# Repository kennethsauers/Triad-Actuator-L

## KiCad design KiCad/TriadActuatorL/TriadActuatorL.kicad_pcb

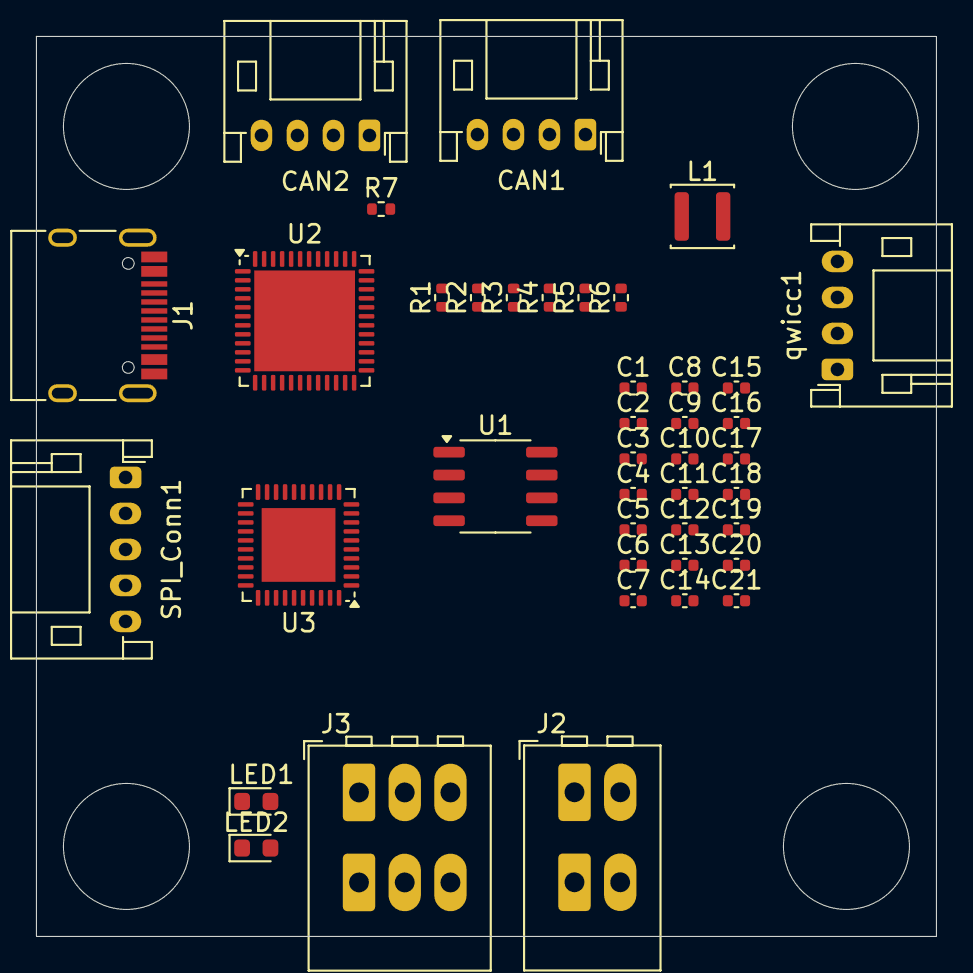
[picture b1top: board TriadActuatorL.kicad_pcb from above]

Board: 2 copper layers, 50.0 x 50.0 mm, 41 parts (0 on the bottom side), 35 nets, no tracks yet.

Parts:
C1, C3, C5, C19, C20: 1uF; C_0402_1005Metric
C2, C4, C6, C7, C21: 100nF; C_0402_1005Metric
C8, C9, C10, C11, C12, C13: 10uF; C_0402_1005Metric
C14, C15, C16: 30pF; C_0402_1005Metric
C17: 22uF; C_0402_1005Metric
C18: 47nF; C_0402_1005Metric
CAN1, CAN2: Conn_01x04_Pin; JST_PH_S4B-PH-K_1x04_P2.00mm_Horizontal
J1: USB_C_Receptacle_USB2.0_16P; USB_C_Receptacle_HRO_TYPE-C-31-M-12
J2: Motor Terminal; TerminalBlock_WAGO_233-502_2x02_P2.54mm
J3: PWR Terminal; TerminalBlock_WAGO_233-503_2x03_P2.54mm
L1: 47uH; L_APV_ANR3015
LED1: red; LED_0603_1608Metric
LED2: blue; LED_0603_1608Metric
R1, R2, R3: 5.1k; R_0402_1005Metric
R4: 330; R_0402_1005Metric
R5, R6, R7: 1000; R_0402_1005Metric
SPI_Conn1: Conn_01x05_Pin; JST_PH_S5B-PH-K_1x05_P2.00mm_Horizontal
U1: MT6701CT; SO-8_3.9x4.9mm_P1.27mm
U2: STM32G431C6Ux; QFN-48-1EP_7x7mm_P0.5mm_EP5.6x5.6mm
U3: DRV8316CRRGFR; HVQFN-40-1EP_6x6mm_P0.5mm_EP4.1x4.1mm
qwicc1: Conn_01x04_Pin; JST_PH_S4B-PH-K_1x04_P2.00mm_Horizontal

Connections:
3V3: C1.1, C2.1, C3.1, C4.1, C5.1, C6.1, C7.1, C21.1, R3.1, U1.1 (VDD), U1.2 (MODE), U2.1 (VBAT), U2.20 (VREF+), U2.21 (VDDA), U2.23 (VDD), U2.35 (VDD), U2.48 (VDD), U3.37 (VREF/ILIM)
BUCK: C17.1, L1.1, U3.3 (FB_BK)
CC1: J1.A5 (CC1), R1.1
CC2: J1.B5 (CC2), R2.1
CUR_A: C14.2, R5.2, U2.8 (PA0)
CUR_B: C15.2, R6.2, U2.9 (PA1)
CUR_C: C16.2, R7.2, U2.10 (PA2)
D+: J1.A6 (D+), J1.B6 (D+), U2.34 (PA12)
D-: J1.A7 (D-), J1.B7 (D-), U2.33 (PA11)
DRV_FAULT: U2.3 (PC14), U3.22 (NFAULT)
DRV_MISO: U2.40 (PC11), U3.33 (SDO)
DRV_MOSI: U2.43 (PB5), U3.34 (SDI)
DRV_NSS: U2.38 (PA15), U3.36 (NSCS)
DRV_OFF: U2.2 (PC13), U3.21 (DRVOFF)
DRV_SCK: U2.39 (PC10), U3.35 (SCLK)
DRV_SLEEP: U2.4 (PC15), U3.23 (NSLEEP)
ENC_MISO: U1.6 (A), U2.14 (PA6)
ENC_NSS: U1.8 (Z), U2.12 (PA4)
ENC_SCK: U1.7 (B), U2.13 (PA5)
GND: C1.2, C2.2, C3.2, C4.2, C5.2, C6.2, C7.2, C8.2, C9.2, C10.2, C11.2, C12.2, C13.2, C14.1, C15.1, C16.1, C17.2, C20.2, C21.2, J1.A1 (GND), J1.A12 (GND), J1.B1 (GND), J1.B12 (GND), J3.2, LED1.1 (K), LED2.1 (K), R1.2, R2.2, U1.4 (GND), U2.49 (VSS), U3.2 (AGND), U3.4 (GND_BK), U3.12 (PGND), U3.15 (PGND), U3.18 (PGND), U3.26 (AGND), U3.41 (EPAD)
unnamed: LED1.2 (A), R3.2
unnamed: LED2.2 (A), R4.2
unnamed: C20.1, U3.25 (AVDD)
unnamed: C19.1, U3.8 (CP)
unnamed: C18.2, U3.7 (CPH)
unnamed: C18.1, U3.6 (CPL)
unnamed: R5.1, U3.40 (SOA)
unnamed: R6.1, U3.39 (SOB)
unnamed: R7.1, U3.38 (SOC)
unnamed: L1.2, U3.5 (SW_BK)
PH_A: J2.1, U3.13 (OUTA), U3.14 (OUTA)
PH_B: J2.2, U3.16 (OUTB), U3.17 (OUTB)
PH_C: U3.19 (OUTC), U3.20 (OUTC)
VBUS: J1.A4 (VBUS), J1.A9 (VBUS), J1.B4 (VBUS), J1.B9 (VBUS)
VIN: C8.1, C9.1, C10.1, C11.1, C12.1, C13.1, C19.2, J3.1, U3.9 (VM), U3.10 (VM), U3.11 (VM)

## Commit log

2025-05-07 Added datasheets
2025-05-07 Added CubeIde File
2025-05-07 Added kicad files
2025-05-07 Added block diagram
2025-05-07 changed GPIO Pinouts
2025-05-07 updated can model
2025-05-09 Added Getting started doc for stm32G4
2025-05-10 updated block diagram
